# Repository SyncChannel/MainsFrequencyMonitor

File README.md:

# MainsFrequencyMonitor

A simple mains frequency monitor using the PIC 16F1619.

Blog post: http://syncchannel.blogspot.com/2016/05/designing-mains-frequency-monitor-part-1.html

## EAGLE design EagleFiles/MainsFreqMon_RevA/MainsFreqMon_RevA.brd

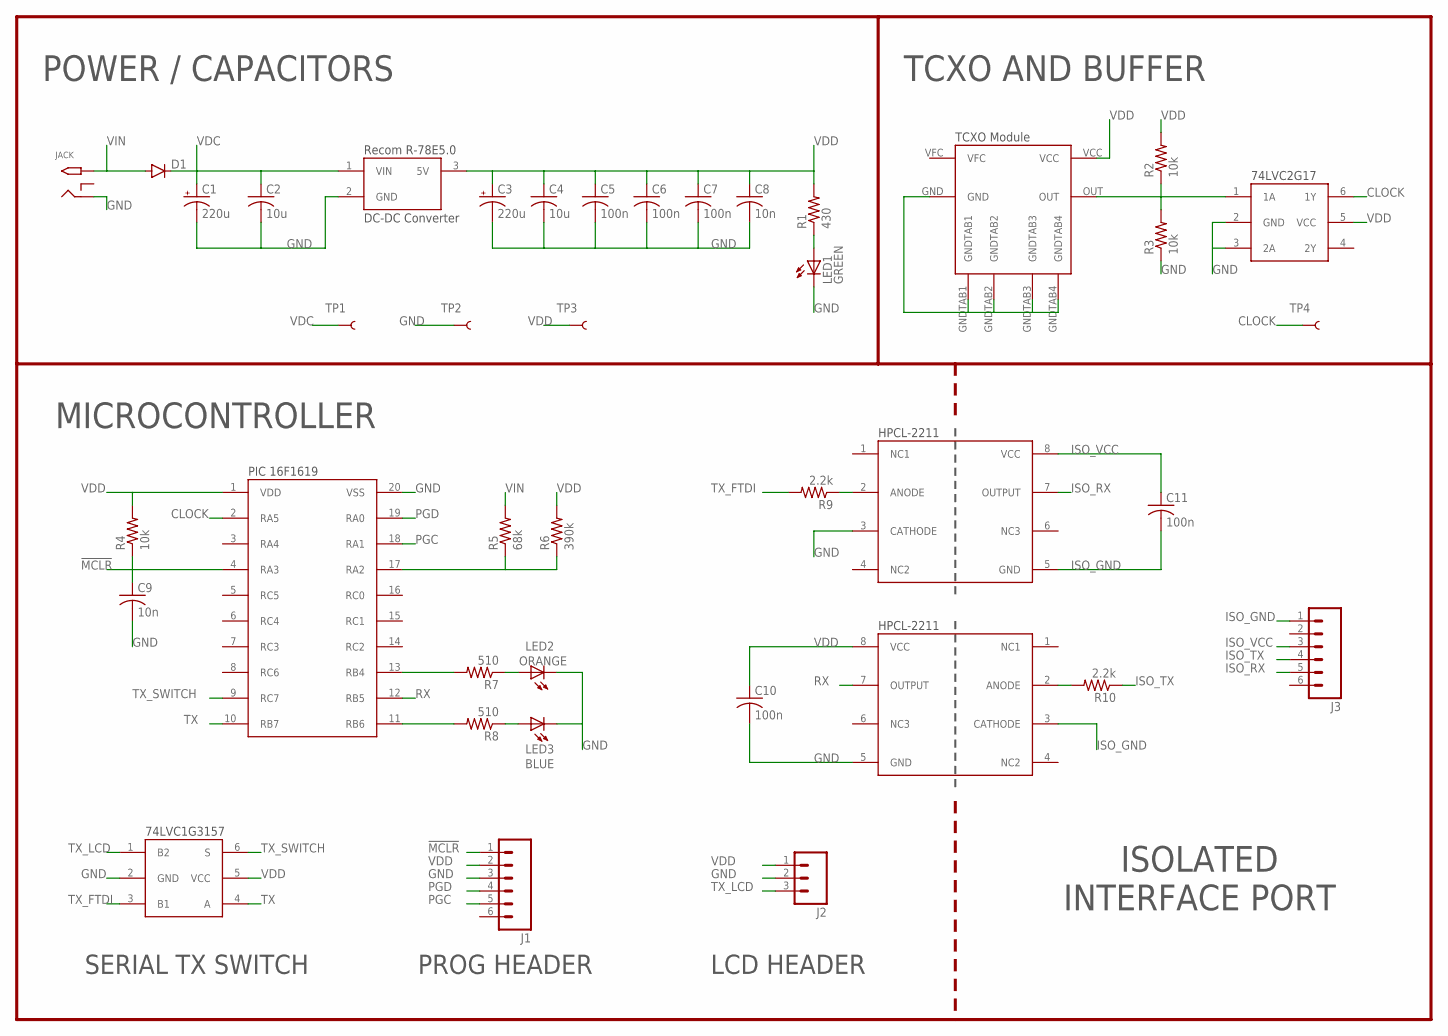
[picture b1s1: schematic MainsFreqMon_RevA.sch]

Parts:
C1, C3: 220u; E3,5-8
C2, C4: 10u; C0805
C5, C6, C7, C10, C11: 100n; C0805
C8, C9: 10n; C0805
D1: DIODEPTH; DIODE-1N4001
J1, J3: M06SILK_FEMALE_PTH; 1X06
J2: M03PTH; 1X03
JACK: 2.1MMJACKTHM; PJ-102A
LED1: GREEN; CHIPLED_1206
LED2: ORANGE; CHIPLED_1206
LED3: BLUE; CHIPLED_1206
R1: 430; R0805
R2, R3, R4: 10k; R0805
R5: 68k; AXIAL-0.4
R6: 390k; AXIAL-0.4
R7, R8: 510; R0805
R9, R10: 2.2k; R0805
RG1: R-78C5.0
TP1, TP2, TP3, TP4: TEST-POINT3X5; PAD.03X.05
U1: 16F1619; SO20L
U2: 74LVC2G14/7; SOT23-6
U3: 74LVC1G3157; SOT23-6
U4, U5: HPCL2211; DIP08
X1: TCXO2

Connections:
!MCLR: C9.1, J1.1, R4.1, U1.4 (RA3)
CLOCK: TP4.P$1, U1.2 (RA5), U2.6 (1Y)
GND: C1.-, C2.2, C3.-, C4.2, C5.2, C6.2, C7.2, C8.2, C9.2, C10.2, J1.3, J2.2, JACK.RING, LED1.C, LED2.C, LED3.C, R3.1, RG1.2 (GND), TP2.P$1, U1.20 (VSS), U2.2 (GND), U2.3 (2A), U3.2 (GND), U4.3 (CATHODE), U5.5 (GND), X1.GND, X1.GNDTAB1, X1.GNDTAB2, X1.GNDTAB3, X1.GNDTAB4
ISO_GND: C11.2, J3.1, U4.5 (GND), U5.3 (CATHODE)
ISO_RX: J3.5, U4.7 (OUTPUT)
ISO_TX: J3.4, R10.1
ISO_VCC: C11.1, J3.3, U4.8 (VCC)
unnamed: R9.1, U4.2 (ANODE)
unnamed: LED1.A, R1.1
unnamed: R10.2, U5.2 (ANODE)
unnamed: R7.2, U1.13 (RB4)
unnamed: R2.1, R3.2, U2.1 (1A), X1.OUT
unnamed: R8.2, U1.11 (RB6)
unnamed: LED2.A, R7.1
unnamed: LED3.A, R8.1
unnamed: R5.P$1 (1), R6.P$1 (1), U1.17 (RA2)
PGC: J1.5, U1.18 (RA1)
PGD: J1.4, U1.19 (RA0)
RX: U1.12 (RB5), U5.7 (OUTPUT)
TX: U1.10 (RB7), U3.4 (A)
TX_FTDI: R9.2, U3.3 (B1)
TX_LCD: J2.3, U3.1 (B2)
TX_SWITCH: U1.9 (RC7), U3.6 (S)
VDC: C1.+, C2.1, D1.C, RG1.1 (VIN), TP1.P$1
VDD: C3.+, C4.1, C5.1, C6.1, C7.1, C8.1, C10.1, J1.2, J2.1, R1.2, R2.2, R4.2, R6.P$2 (2), RG1.3 (5V), TP3.P$1, U1.1 (VDD), U2.5 (VCC), U3.5 (VCC), U5.8 (VCC), X1.VCC
VIN: D1.A, JACK.TIP, R5.P$2 (2)

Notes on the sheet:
DC-DC Converter
TCXO Module
POWER / CAPACITORS
TCXO AND BUFFER
MICROCONTROLLER
74LVC1G3157
SERIAL TX SWITCH
PROG HEADER
PIC 16F1619
HPCL-2211
ISOLATED INTERFACE PORT
LCD HEADER
74LVC2G17
Recom R-78E5.0

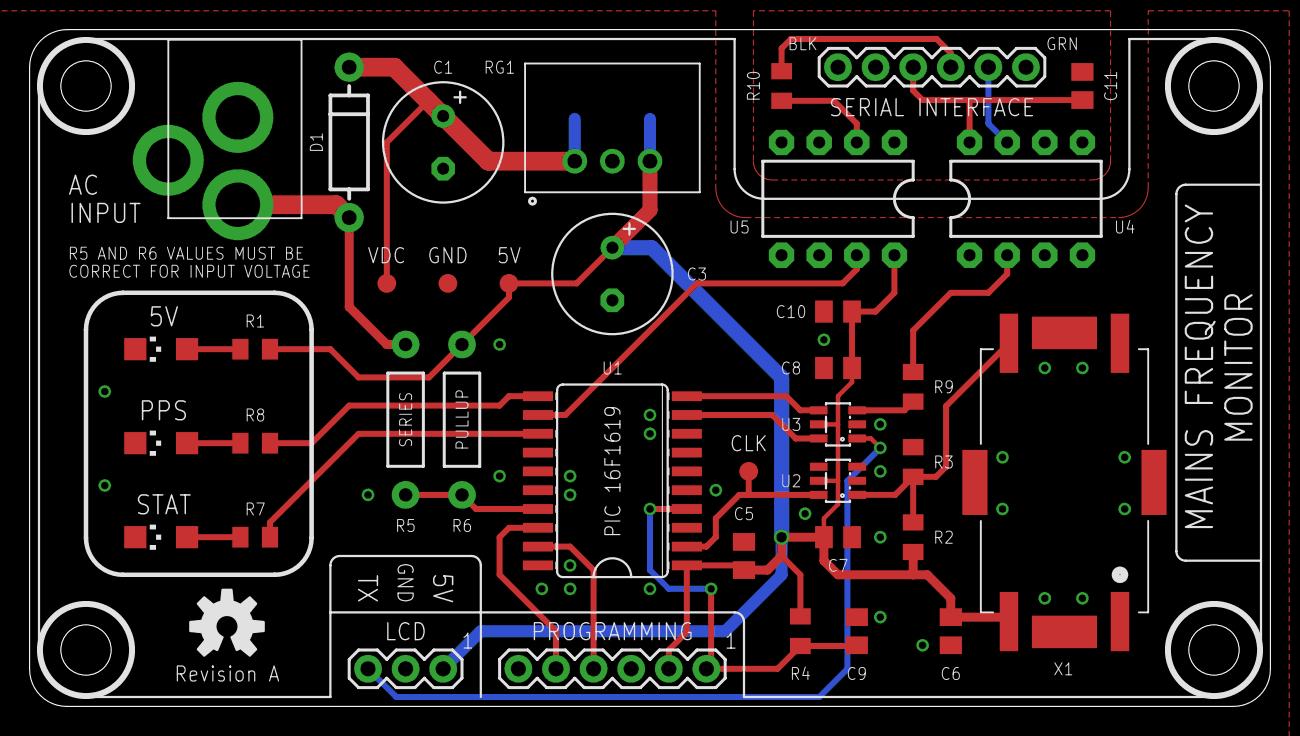
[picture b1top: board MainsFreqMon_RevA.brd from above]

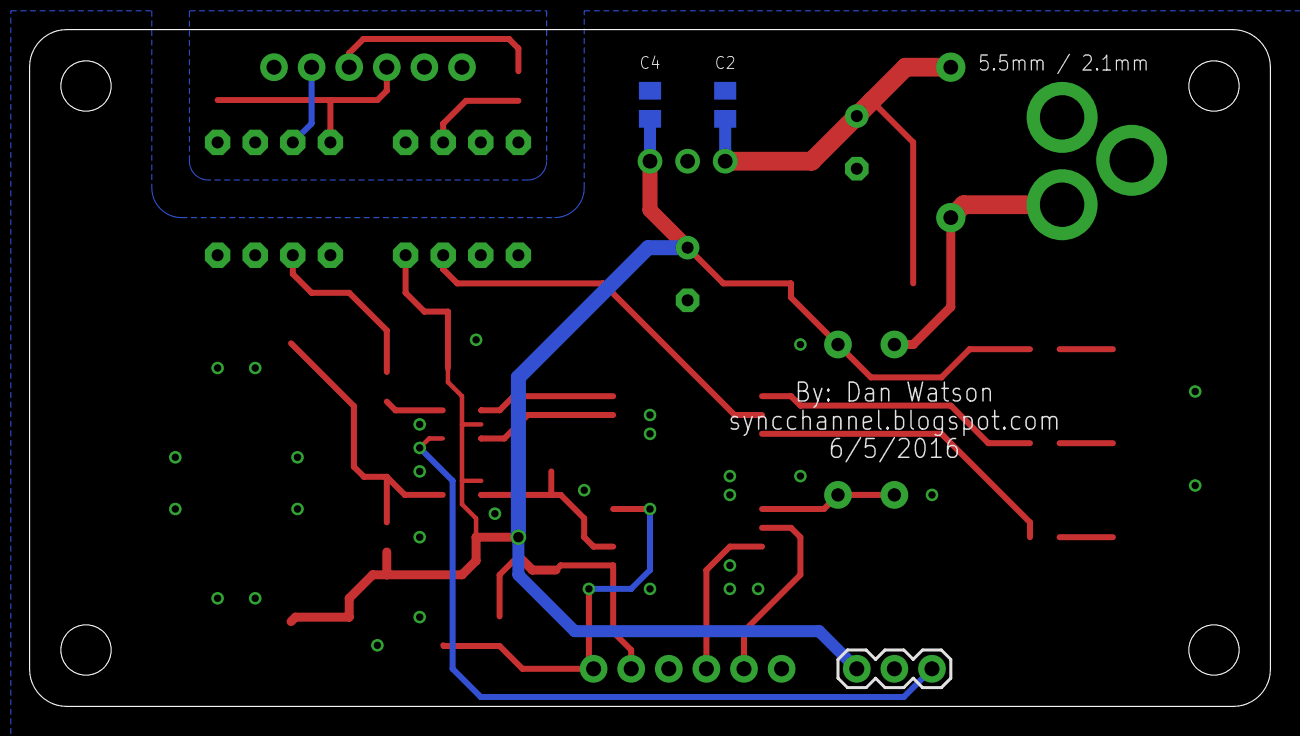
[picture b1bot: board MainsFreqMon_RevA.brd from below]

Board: 2 copper layers, 83.8 x 45.7 mm, 41 parts (2 on the bottom side), 26 nets.

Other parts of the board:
U$1: OSHW-LOGO-M

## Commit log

2016-05-17 :tada: Added .gitattributes & .gitignore files
2016-05-17 Added MPLAB project
2016-05-17 Added Readme
2016-06-20 Added Eagle files, updated firmware

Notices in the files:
parts and their libraries:
SparkFun-DiscreteSemi: Licensing: Creative Commons ShareAlike 4.0 International - https://creativecommons.org/licenses/by-sa/4.0
